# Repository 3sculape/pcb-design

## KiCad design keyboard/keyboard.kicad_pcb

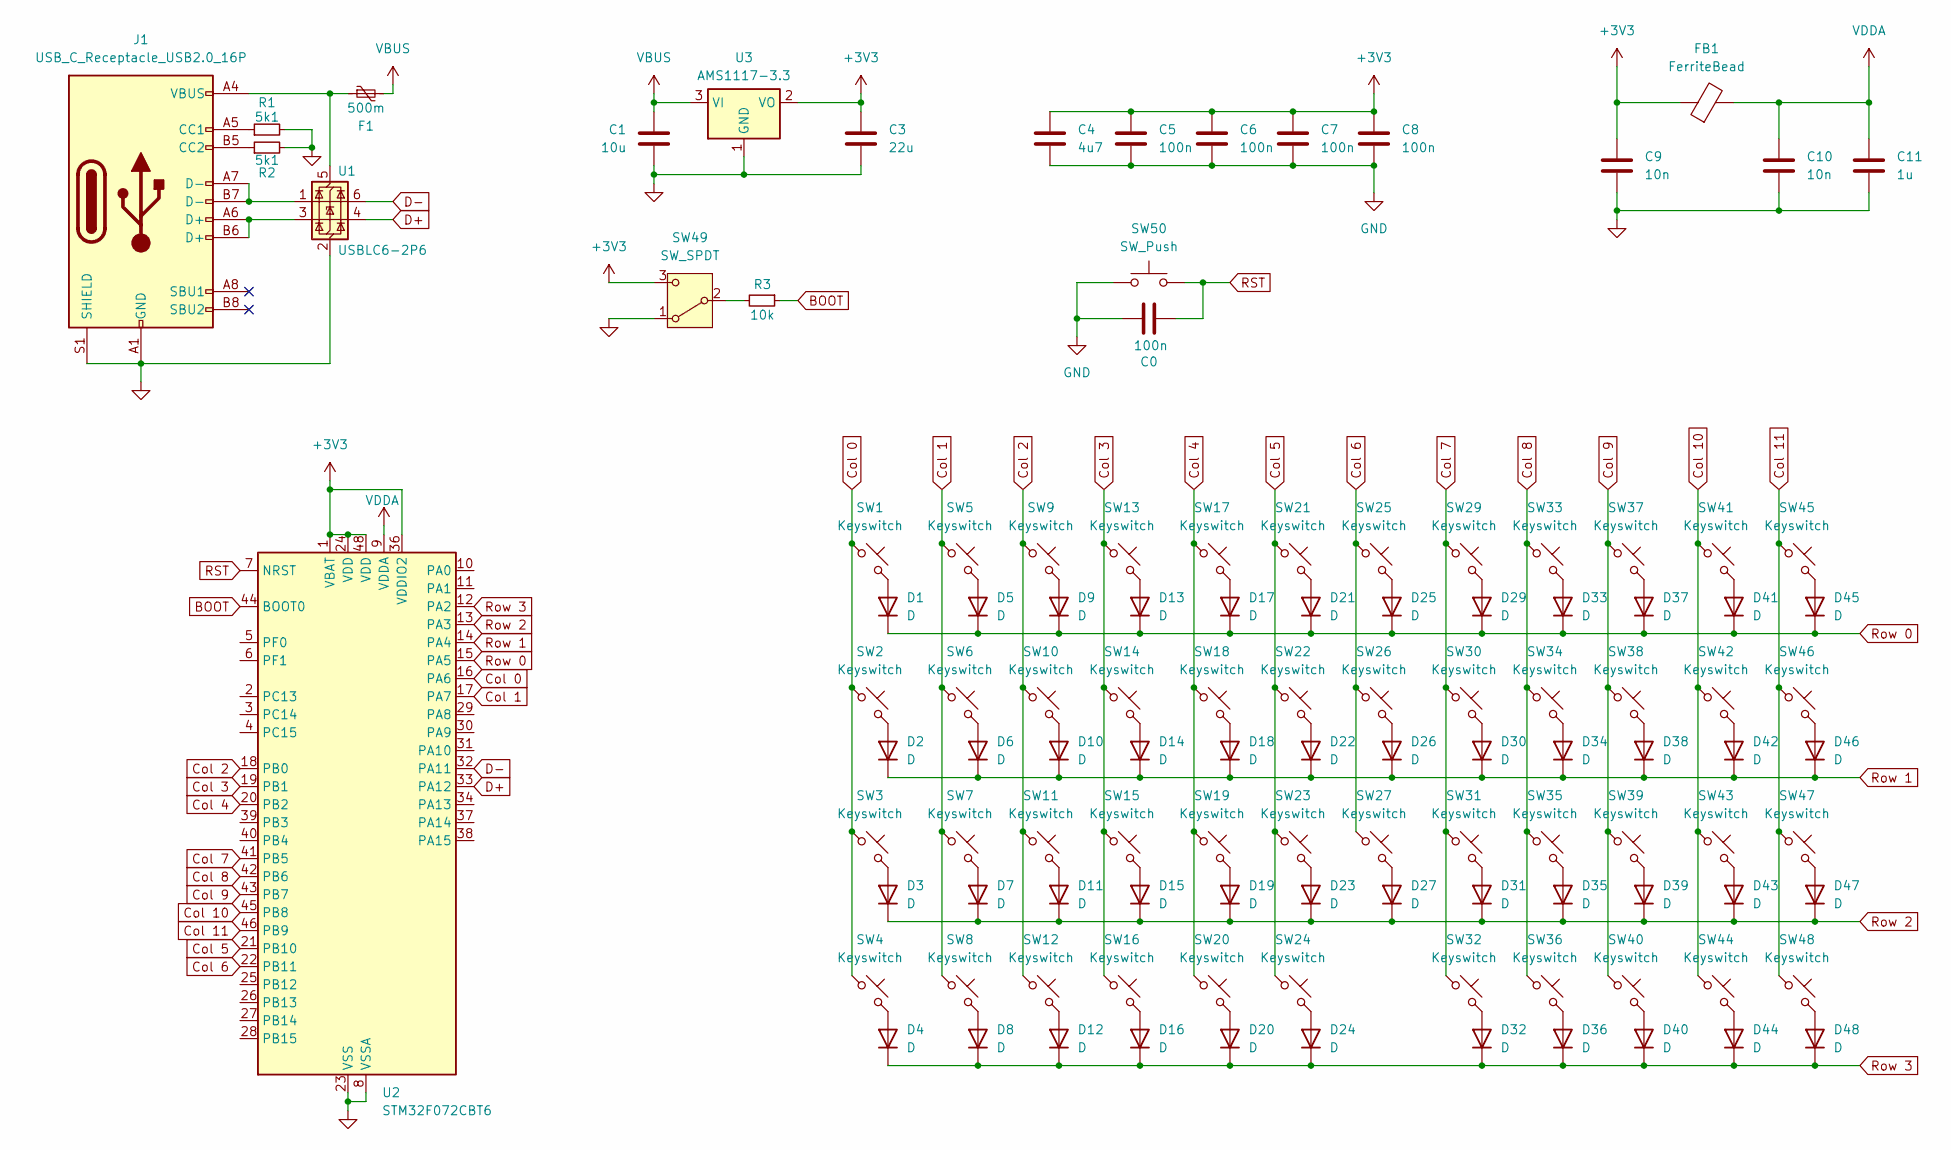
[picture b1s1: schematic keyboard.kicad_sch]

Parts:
C0, C5, C6, C7, C8: 100n; C_0603_1608Metric; JLC 0603
C1: 10u; C_0603_1608Metric; JLC 0603
C3: 22u; C_0603_1608Metric; JLC 0603
C4: 4u7; C_0603_1608Metric; JLC 0603
C9, C10: 10n; C_0603_1608Metric; JLC 0603
C11: 1u; C_0603_1608Metric; JLC 0603
D1, D2, D3, D4, D5, D6, D7, D8, D9, D10, D11, D12, D13, D14, D15, D16, D17, D18, D19, D20, D21, D22, D23, D24, D25, D26, D27, D29, D30, D31, D32, D33, D34, D35, D36, D37, D38, D39, D40, D41, D42, D43, D44, D45, D46, D47, D48: D; D_SOD-123; JLC SOD-123
F1: 500m; Fuse_0603_1608Metric; JLC 0603
FB1: FerriteBead; L_0603_1608Metric; JLC 0603
J1: USB_C_Receptacle_USB2.0_16P; USB_C_Receptacle_XKB_U262-16XN-4BVC11; JLC SMD
R1, R2: 5k1; R_0603_1608Metric; JLC 0603
R3: 10k; R_0603_1608Metric; JLC 0603
SW1, SW2, SW3, SW4, SW5, SW6, SW7, SW8, SW9, SW10, SW11, SW12, SW13, SW14, SW15, SW16, SW17, SW18, SW19, SW20, SW21, SW22, SW23, SW24, SW25, SW26, SW27, SW29, SW30, SW31, SW32, SW33, SW34, SW35, SW36, SW37, SW38, SW39, SW40, SW41, SW42, SW43, SW44, SW45, SW46, SW47, SW48: Keyswitch; SW_Hotswap_Kailh_MX; JLC SMD
SW49: SW_SPDT; SW_SPDT_PCM12; JLC SMD
SW50: SW_Push; SW_SPST_SKQG_WithStem; JLC SMD
U1: USBLC6-2P6; SOT-666; JLC SOT-666-6
U2: STM32F072CBT6; LQFP-48_7x7mm_P0.5mm; JLC LQFP-48(7x7)
U3: AMS1117-3.3; SOT-223-3_TabPin2; JLC SOT-223

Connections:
+3V3: C3.1, C4.1, C5.1, C6.1, C7.1, C8.1, C9.1, FB1.1, SW49.3 (C), U2.1 (VBAT), U2.24 (VDD), U2.36 (VDDIO2), U2.48 (VDD), U3.2 (VO)
BOOT: R3.1, U2.44 (BOOT0)
Col 0: SW1.1, SW2.1, SW3.1, SW4.1, U2.16 (PA6)
Col 1: SW5.1, SW6.1, SW7.1, SW8.1, U2.17 (PA7)
Col 2: SW9.1, SW10.1, SW11.1, SW12.1, U2.18 (PB0)
Col 3: SW13.1, SW14.1, SW15.1, SW16.1, U2.19 (PB1)
Col 4: SW17.1, SW18.1, SW19.1, SW20.1, U2.20 (PB2)
Col 5: SW21.1, SW22.1, SW23.1, SW24.1, U2.21 (PB10)
Col 6: SW25.1, SW26.1, SW27.1, U2.22 (PB11)
Col 7: SW29.1, SW30.1, SW31.1, SW32.1, U2.41 (PB5)
Col 8: SW33.1, SW34.1, SW35.1, SW36.1, U2.42 (PB6)
Col 9: SW37.1, SW38.1, SW39.1, SW40.1, U2.43 (PB7)
Col 10: SW41.1, SW42.1, SW43.1, SW44.1, U2.45 (PB8)
Col 11: SW45.1, SW46.1, SW47.1, SW48.1, U2.46 (PB9)
D+: U1.4 (I/O2), U2.33 (PA12)
D-: U1.6 (I/O1), U2.32 (PA11)
GND: C0.2, C1.2, C3.2, C4.2, C5.2, C6.2, C7.2, C8.2, C9.2, C10.2, C11.2, J1.A1 (GND), J1.A12 (GND), J1.B1 (GND), J1.B12 (GND), J1.S1 (SHIELD), R1.2, R2.2, SW49.1 (A), SW50.1, U1.2 (GND), U2.8 (VSSA), U2.23 (VSS), U2.35 (VSS), U2.47 (VSS), U3.1 (GND)
unnamed: D1.2 (A), SW1.2
unnamed: D2.2 (A), SW2.2
unnamed: D3.2 (A), SW3.2
unnamed: D4.2 (A), SW4.2
unnamed: D5.2 (A), SW5.2
unnamed: D6.2 (A), SW6.2
unnamed: D7.2 (A), SW7.2
unnamed: D8.2 (A), SW8.2
unnamed: D9.2 (A), SW9.2
unnamed: D10.2 (A), SW10.2
unnamed: D11.2 (A), SW11.2
unnamed: D12.2 (A), SW12.2
unnamed: D13.2 (A), SW13.2
unnamed: D14.2 (A), SW14.2
unnamed: D15.2 (A), SW15.2
unnamed: D16.2 (A), SW16.2
unnamed: D17.2 (A), SW17.2
unnamed: D18.2 (A), SW18.2
unnamed: D19.2 (A), SW19.2
unnamed: D20.2 (A), SW20.2
unnamed: D21.2 (A), SW21.2
unnamed: D22.2 (A), SW22.2
unnamed: D23.2 (A), SW23.2
unnamed: D24.2 (A), SW24.2
unnamed: D25.2 (A), SW25.2
unnamed: D26.2 (A), SW26.2
unnamed: D27.2 (A), SW27.2
unnamed: D29.2 (A), SW29.2
unnamed: D30.2 (A), SW30.2
unnamed: D31.2 (A), SW31.2
unnamed: D32.2 (A), SW32.2
unnamed: D33.2 (A), SW33.2
unnamed: D34.2 (A), SW34.2
unnamed: D35.2 (A), SW35.2
unnamed: D36.2 (A), SW36.2
unnamed: D37.2 (A), SW37.2
unnamed: D38.2 (A), SW38.2
unnamed: D39.2 (A), SW39.2
unnamed: D40.2 (A), SW40.2
unnamed: D41.2 (A), SW41.2
unnamed: D42.2 (A), SW42.2
unnamed: D43.2 (A), SW43.2
unnamed: D44.2 (A), SW44.2
unnamed: D45.2 (A), SW45.2
unnamed: D46.2 (A), SW46.2
unnamed: D47.2 (A), SW47.2
unnamed: D48.2 (A), SW48.2
unnamed: J1.A5 (CC1), R1.1
unnamed: J1.B5 (CC2), R2.1
unnamed: J1.A6 (D+), J1.B6 (D+), U1.3 (I/O2)
unnamed: J1.A7 (D-), J1.B7 (D-), U1.1 (I/O1)
unnamed: R3.2, SW49.2 (B)
unnamed: F1.1, J1.A4 (VBUS), J1.A9 (VBUS), J1.B4 (VBUS), J1.B9 (VBUS), U1.5 (VBUS)
RST: C0.1, SW50.2, U2.7 (NRST)
Row 0: D1.1 (K), D5.1 (K), D9.1 (K), D13.1 (K), D17.1 (K), D21.1 (K), D25.1 (K), D29.1 (K), D33.1 (K), D37.1 (K), D41.1 (K), D45.1 (K), U2.15 (PA5)
Row 1: D2.1 (K), D6.1 (K), D10.1 (K), D14.1 (K), D18.1 (K), D22.1 (K), D26.1 (K), D30.1 (K), D34.1 (K), D38.1 (K), D42.1 (K), D46.1 (K), U2.14 (PA4)
Row 2: D3.1 (K), D7.1 (K), D11.1 (K), D15.1 (K), D19.1 (K), D23.1 (K), D27.1 (K), D31.1 (K), D35.1 (K), D39.1 (K), D43.1 (K), D47.1 (K), U2.13 (PA3)
Row 3: D4.1 (K), D8.1 (K), D12.1 (K), D16.1 (K), D20.1 (K), D24.1 (K), D32.1 (K), D36.1 (K), D40.1 (K), D44.1 (K), D48.1 (K), U2.12 (PA2)
VBUS: C1.1, F1.2, U3.3 (VI)
VDDA: C10.1, C11.1, FB1.2, U2.9 (VDDA)

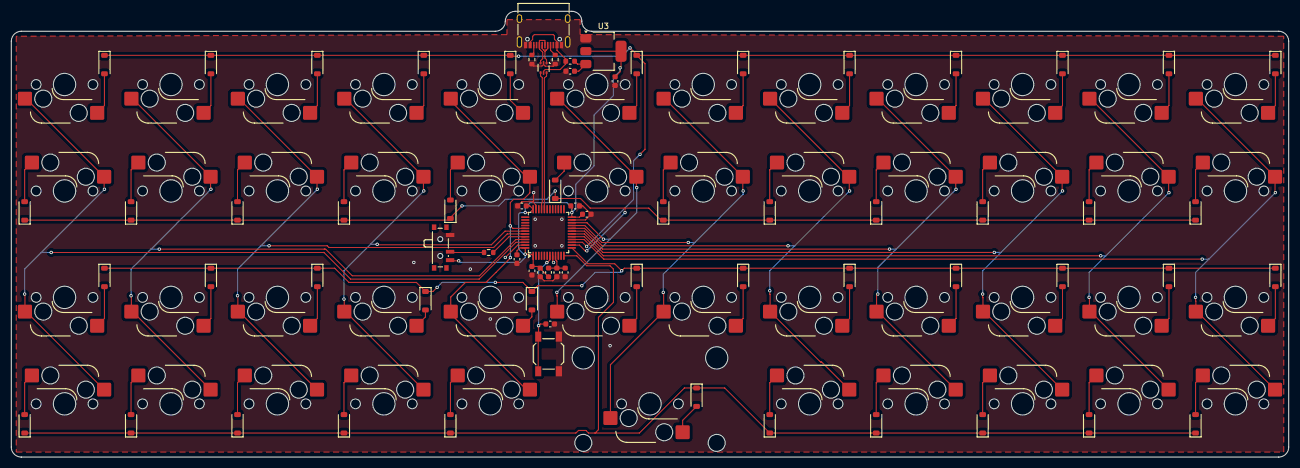
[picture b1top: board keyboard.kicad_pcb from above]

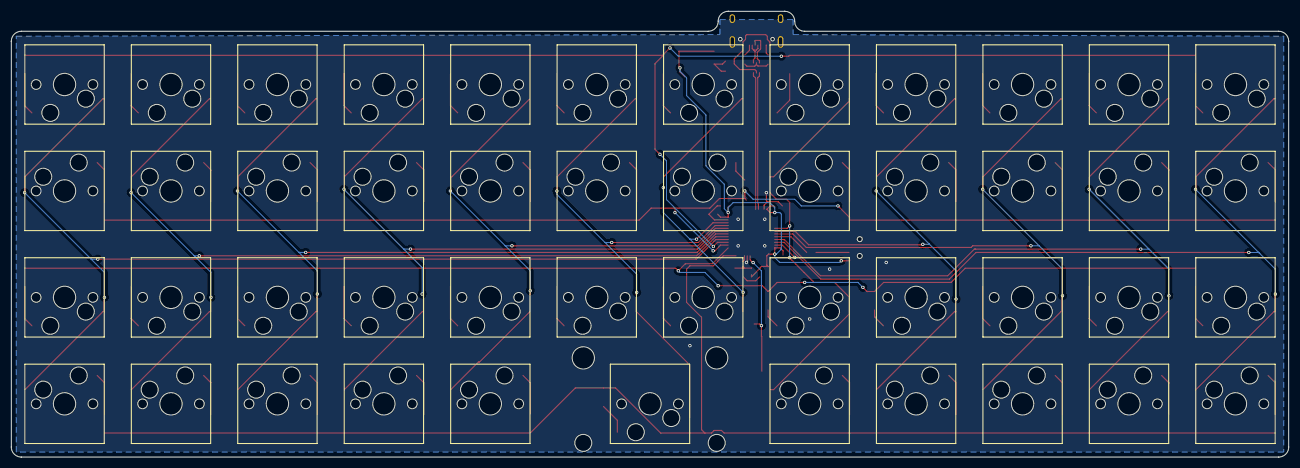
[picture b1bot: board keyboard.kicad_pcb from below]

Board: 2 copper layers, 228.6 x 79.8 mm, 116 parts (47 on the bottom side), 77 nets.

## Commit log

2024-08-02 feat(keyboard): init
2024-08-06 feat(keyboard): add power supplies
2024-08-08 feat(keyboard): add boot, rst and usb
2024-08-11 feat(keyboard): pcb route
2024-08-11 feat(keyboard): finish route, edges and silk
2024-08-11 feat(keyboard): fix bom and cpl
2024-08-13 feat(keyboard): changed from QFP48 to LQFP48
